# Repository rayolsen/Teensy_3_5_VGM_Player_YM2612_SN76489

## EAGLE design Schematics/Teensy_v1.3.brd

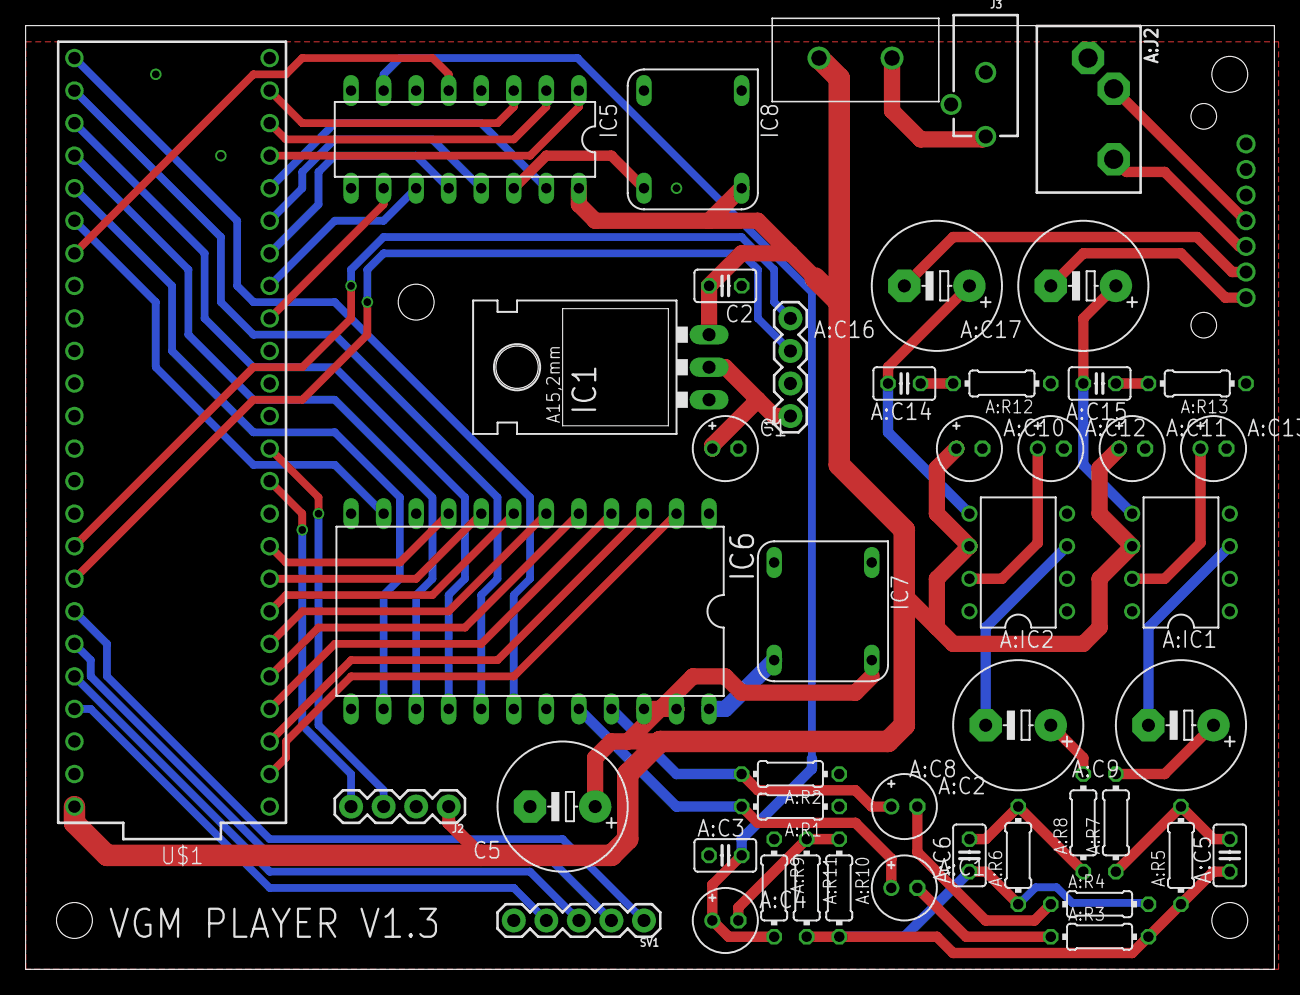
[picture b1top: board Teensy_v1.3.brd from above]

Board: 2 copper layers, 97.5 x 73.7 mm, 47 parts (0 on the bottom side), 61 nets.

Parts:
A:C1, A:C2: 10uF; E2-5
A:C3: 220pF; C025-025X050
A:C4: 1uF; E2-5
A:C5, A:C6: 4.7nF; C025-025X050
A:C8, A:C9: 16uF; E5-10,5
A:C10, A:C11, A:C12, A:C13: 100uF; E2-5
A:C14, A:C15: 47nF; C025-025X050
A:C16, A:C17: 1000uF; E5-10,5
A:IC1, A:IC2: LM386N-1; DIL08
A:J2: SJ1-3533NG
A:R1, A:R2, A:R3, A:R4, A:R9: 2.2k; 0204/7
A:R5, A:R6: 10k; 0204/7
A:R7, A:R8: 11k; 0204/7
A:R10, A:R11: 51k; 0204/7
A:R12, A:R13: 10; 0204/7
A:U$1: P140KV1; P14O
C1: 10uF; E2-5
C2: 100nF; C025-025X050
C5: 1000uF; E5-10,5
IC1: LD117AV33; TO220L1
IC5: SN; DIL16
IC6: YM; DIL24-6
IC7: 7.68MHz; DIL08-CLK
IC8: 3.57MHz; DIL08-CLK
J1: OLED_128X64_I2C; 1X04
J2: HC-06; 1X04
J3: POWER_JACK; POWER_JACK_PTH
SV1: 1X05
U$1: TEENSY_3.5_DIL
U$7: GPTS20; GPTS

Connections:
5V: A:C10.+, A:C11.+, A:IC1.6, A:IC2.6, C2.2, C5.+, IC1.3, IC5.16, IC6.22, IC6.23, IC7.5V, IC8.5V, J2.1, U$1.VIN, U$7.P$1
A:N$1: A:C16.-, A:U$1.1
A:N$2: A:C17.-, A:U$1.1'
A:N$3: A:C15.2, A:C17.+, A:IC1.5
A:N$4: A:C14.2, A:C16.+, A:IC2.5
A:N$5: A:C13.+, A:IC1.7
A:N$6: A:C12.+, A:IC2.7
A:N$7: A:C9.-, A:IC1.3
A:N$8: A:C8.-, A:IC2.3
A:N$9: A:C9.+, A:R7.2
A:N$10: A:C8.+, A:R8.2
A:N$11: A:C15.1, A:R13.2
A:N$12: A:C14.1, A:R12.2
A:N$13: A:C6.1, A:R4.2, A:R6.1, A:R10.2
A:N$14: A:C5.1, A:R3.2, A:R5.1, A:R11.2
A:N$15: A:C4.-, A:R10.1, A:R11.1
A:N$16: A:C1.-, A:R3.1
A:N$17: A:C2.-, A:R4.1
A:N$18: A:C5.2, A:R5.2, A:R7.1
A:N$19: A:C6.2, A:R6.2, A:R8.1
A:N$20: A:J2.2, A:U$1.2'
A:N$21: A:J2.3, A:U$1.2
BUTTON1: SV1.1, U$1.20/A6
BUTTON2: SV1.2, U$1.21/A7
BUTTON3: SV1.3, U$1.22/A8
BUTTON4: SV1.4, U$1.23/A9
GND: A:C3.1, A:C10.-, A:C11.-, A:C12.-, A:C13.-, A:IC1.2, A:IC1.4, A:IC2.2, A:IC2.4, A:J2.1, A:R1.1, A:R2.1, A:R9.1, A:R12.1, A:R13.1, A:U$1.3, A:U$1.3', C1.-, C2.1, C5.-, IC1.1, IC5.6, IC5.8, IC6.1, IC6.19, IC7.GND, IC8.GND, J1.2, J2.2, J3.GND, J3.GNDBREAK, SV1.5, U$1.GND, U$1.GND1
I2C_SCL: J1.3, U$1.19/A5
I2C_SDA: J1.4, U$1.18/A4
unnamed: IC6.24, IC7.5
unnamed: J3.PWR, U$7.P$2
unnamed: IC5.14, IC8.5
RX: J2.3, U$1.10
SN_D0: IC5.10, U$1.24
SN_D1: IC5.11, U$1.25
SN_D2: IC5.12, U$1.26
SN_D3: IC5.13, U$1.27
SN_D4: IC5.15, U$1.28
SN_D5: IC5.1, U$1.29
SN_D6: IC5.2, U$1.30
SN_D7: IC5.3, U$1.31/A12
SN_OUT: A:C3.2, A:C4.+, A:R9.2, IC5.7
SN_WE: IC5.5, U$1.39/A20
TX: J2.4, U$1.9
VCC: C1.+, IC1.2, J1.1
YM_A0: IC6.17, U$1.34/A15
YM_A1: IC6.18, U$1.33/A14
YM_CS: IC6.14, U$1.37/A18
YM_D0: IC6.2, U$1.0
YM_D1: IC6.3, U$1.1
YM_D2: IC6.4, U$1.2
YM_D3: IC6.5, U$1.3
YM_D4: IC6.6, U$1.4
YM_D5: IC6.7, U$1.5
YM_D6: IC6.8, U$1.6
YM_D7: IC6.9, U$1.7
YM_IC: IC6.11, U$1.38/A19
YM_MOL: A:C2.+, A:R2.2, IC6.21
YM_MOR: A:C1.+, A:R1.2, IC6.20
YM_RD: IC6.16, U$1.35/A16
YM_WR: IC6.15, U$1.36/A17

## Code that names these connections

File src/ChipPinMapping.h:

typedef unsigned char byte;
//YM_DATA
byte YM_DATA[8] = {0,1,2,3,4,5,6,7};

//YM_CONTROL
#define YM_IC 38
#define YM_CS 37
#define YM_WR 36
#define YM_RD 35
#define YM_A0 34
#define YM_A1 33

//SN_DATA
byte SN_DATA[8] = {24, 25, 26, 27, 28, 29, 30, 31};

//SN_CONTROL
#define SN_WE 39

//LTC6903 External Clocks
//#define SN_CLOCK_CS 32
//#define YM_CLOCK_CS 14

//External Buttons
#define FWD_BTN 23
#define RNG_BTN 22
#define PRV_BTN 21
#define PSE_BTN 20

//UART Bluetooth module
//Serial2 defined by Teensy spec
#define BT_RX 9
#define BT_TX 10
// #define HWSERIAL Serial2
//Debug LED
//#define PIN_D13 13

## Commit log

2017-10-03 Pausing
    Added Pause playback and omit screen stuff
2017-12-14 debugging attempts
2018-01-02 combined files and added to rep
2018-01-02 More Documents and file organizing
2018-01-05 new version to address issues
2018-02-13 Total Resdesign
    This should probably be considered a 2.0 rev
2018-07-16 Uncommented BT code, not working yet
2018-08-17 force bt serial for testing
2018-08-28 adding hc06 data sheet
2018-09-04 All serial > serial2 BT working

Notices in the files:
parts and their libraries:
con-cuistack: Copyright (C) 2008, Bob Starr
SparkFun-Connectors: Licensing: Creative Commons ShareAlike 4.0 International - https://creativecommons.org/licenses/by-sa/4.0
